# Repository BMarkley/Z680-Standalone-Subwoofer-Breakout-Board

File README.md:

# Z680-Standalone-Subwoofer-Breakout-Board

This is a pcb and circuit for repurposing the subwoofer in the Z680 Logitech speakers system with an aftermarket receiver. Good for keeping these speakers in service after the control pod fails.

The PCB has been tested and works great, but the design is provided with no garauntees or warranty. You are liable for your own actions.

Notes on the LED and enclosure: 

1: The enclosure took a little trial and error so use your best judgement. The original plan for the LED was to lave it illuminate the phono jack but the LED I selected was not bright enough to work like that. I had to bring it to the exterior of the case. Inconsistencies in the photos are just the trial and error process. 

2: I needed to use 2 washers on the potentiometer to get the Dsub connector to be at the correct depth.

3: You may want to use double sided tape to secure the final product to the back of the subwoofer. 

Licensing: Open Hardware licensed under the Creative Commons BY-SA 4.0 License

You are free to:
Share — copy and redistribute the material in any medium or format
Adapt — remix, transform, and build upon the material
The licensor cannot revoke these freedoms as long as you follow the license terms.
Under the following terms:
Attribution — You must give appropriate credit, provide a link to the license, and indicate if changes were made. You may do so in any reasonable manner, but not in any way that suggests the licensor endorses you or your use.

NonCommercial — You may not use the material for commercial purposes.

ShareAlike — If you remix, transform, or build upon the material, you must distribute your contributions under the same license as the original.

No additional restrictions — You may not apply legal terms or technological measures that legally restrict others from doing anything the license permits.

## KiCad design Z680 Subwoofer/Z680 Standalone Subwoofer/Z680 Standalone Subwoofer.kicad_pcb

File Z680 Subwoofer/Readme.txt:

This is a pcb and circuit for repurposing the subwoofer in the Z680 Logitech speakers system with an aftermarket receiver. Good for keeping these speakers in service after the control pod fails.

The PCB has been tested and works great, but the design is provided with no garauntees or warranty. You are liable for your own actions.

Notes on the LED and enclosure: 
1: The enclosure took a little trial and error so use your best judgement. The original plan for the LED was to lave it illuminate the phono jack but the LED I selected was not bright enough to work like that. I had to bring it to the exterior of the case. Inconsistencies in the photos are just the trial and error process. 
2: I needed to use 2 washers on the potentiometer to get the Dsub connector to be at the correct depth.
3: You may want to use double sided tape to secure the final product to the back of the subwoofer. 

Licensing: Open Hardware licensed under the Creative Commons BY-SA 4.0 License

You are free to:
Share — copy and redistribute the material in any medium or format
Adapt — remix, transform, and build upon the material
The licensor cannot revoke these freedoms as long as you follow the license terms.
Under the following terms:
Attribution — You must give appropriate credit, provide a link to the license, and indicate if changes were made. You may do so in any reasonable manner, but not in any way that suggests the licensor endorses you or your use.

NonCommercial — You may not use the material for commercial purposes.

ShareAlike — If you remix, transform, or build upon the material, you must distribute your contributions under the same license as the original.

No additional restrictions — You may not apply legal terms or technological measures that legally restrict others from doing anything the license permits.

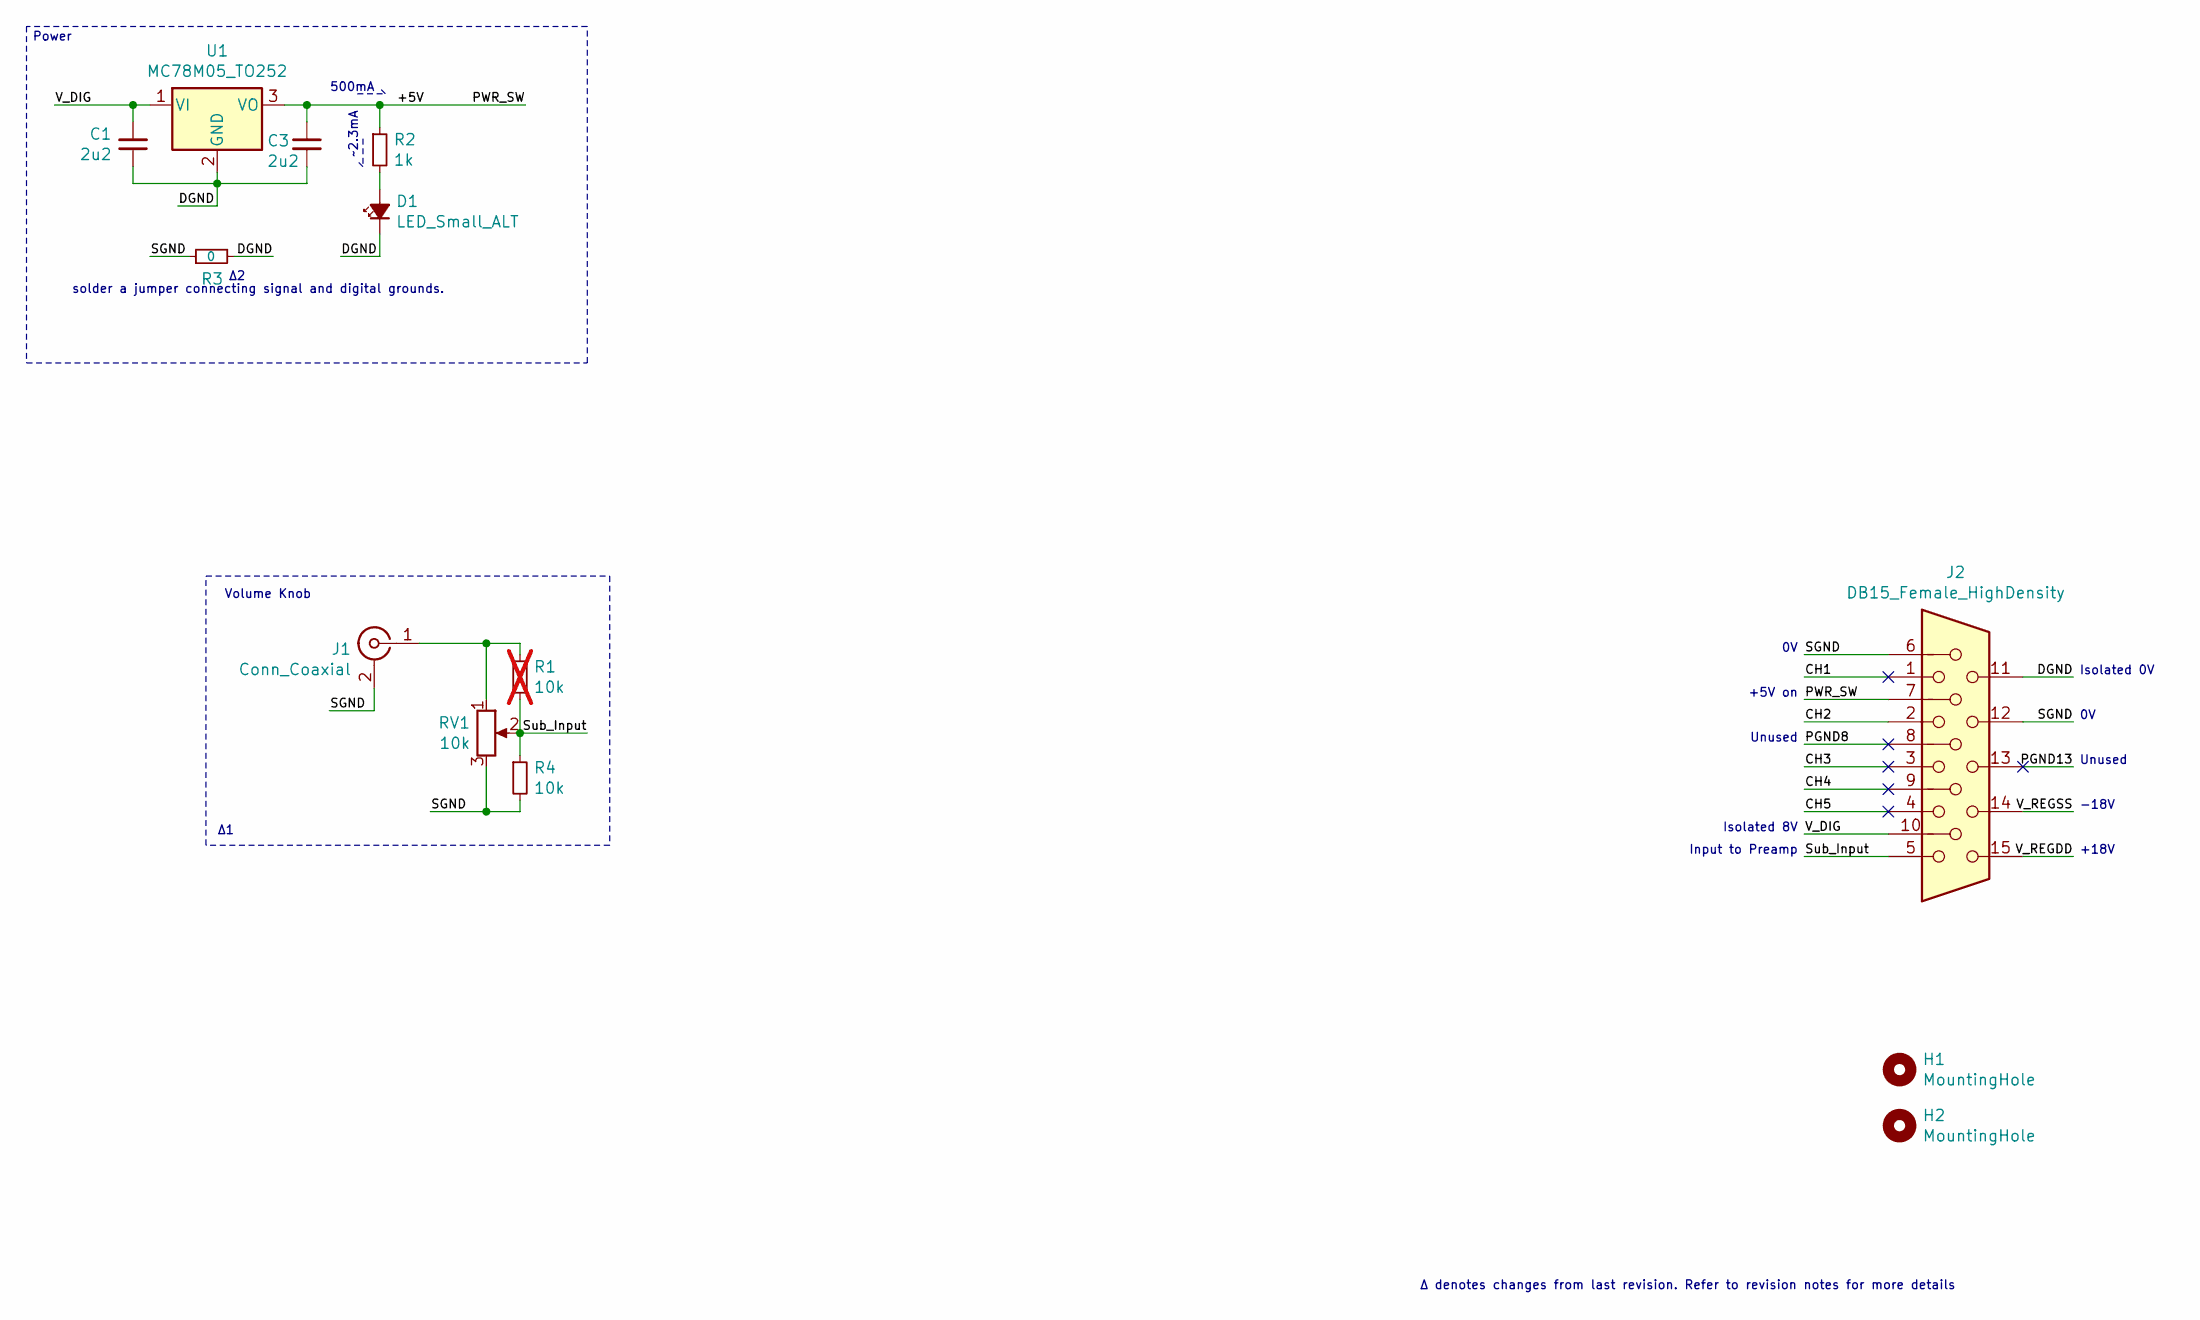
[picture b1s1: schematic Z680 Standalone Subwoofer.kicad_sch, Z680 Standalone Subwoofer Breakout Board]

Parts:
C1, C3: 2u2; C_0805_2012Metric
D1: LED_Small_ALT; LED_D3.0mm_Clear
H1, H2: MountingHole; MountingHole_2.2mm_M2
J1: Conn_Coaxial; RCJ-02
J2: DB15_Female_HighDensity; DSUB-15-HD_Female_Vertical_P2.29x1.98mm_MountingHoles
R1: 10k; R_0603_1608Metric; not fitted
R2: 1k; R_0603_1608Metric
R3: 0; R_0805_2012Metric
R4: 10k; R_0603_1608Metric
RV1: 10k; PotentiometerRecessed
U1: MC78M05_TO252; TO-252-2

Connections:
/+5V: C3.1, J2.7, R2.1, U1.3 (VO)
/CH1: J2.1
/CH2: J2.2
/CH3: J2.3
/CH4: J2.9
/CH5: J2.4
/DGND: C1.1, C3.2, D1.1 (K), J2.11, R3.2, U1.2 (GND)
/PGND8: J2.8
/PGND13: J2.13
/SGND: J1.2 (Ext), J2.6, J2.12, R3.1, R4.2, RV1.3
/Sub_Input: J2.5, R1.2, R4.1, RV1.2
/V_DIG: C1.2, J2.10, U1.1 (VI)
/V_REGDD: J2.15
/V_REGSS: J2.14
unnamed: D1.2 (A), R2.2
unnamed: J1.1 (In), R1.1, RV1.1

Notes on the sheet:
Input to Preamp
solder a jumper connecting signal and digital grounds.
~2.3mA
Volume Knob
-18V
Unused
500mA
Power
+18V
Δ denotes changes from last revision. Refer to revision notes for more details
Isolated 8V
+5V on
Isolated 0V

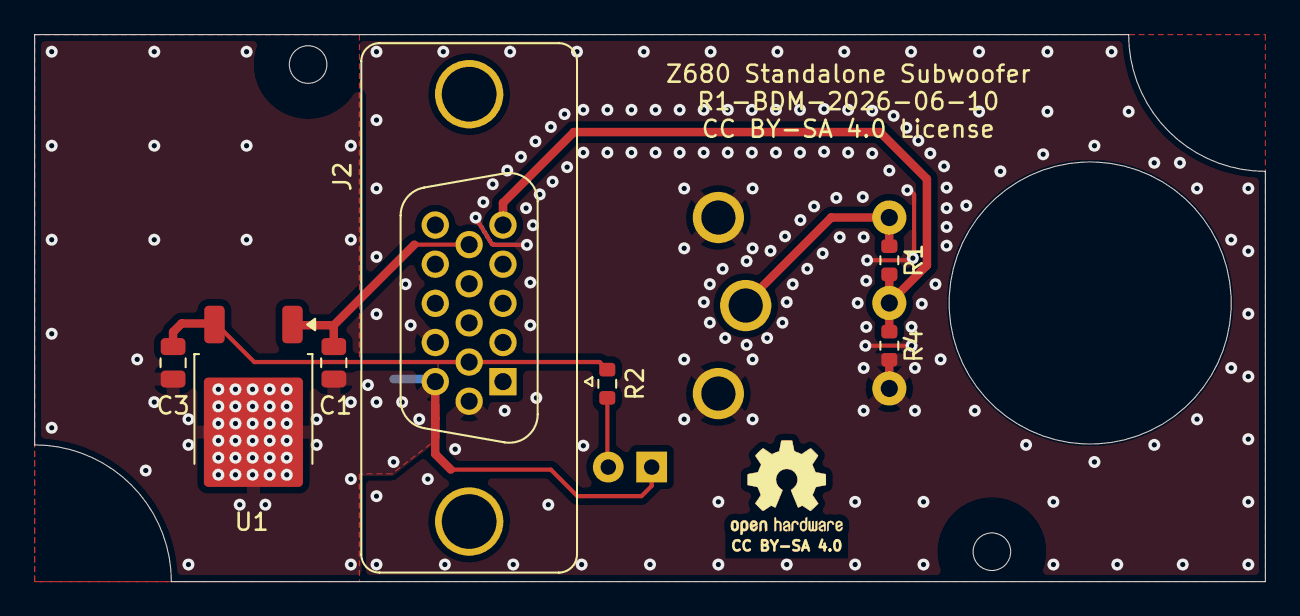
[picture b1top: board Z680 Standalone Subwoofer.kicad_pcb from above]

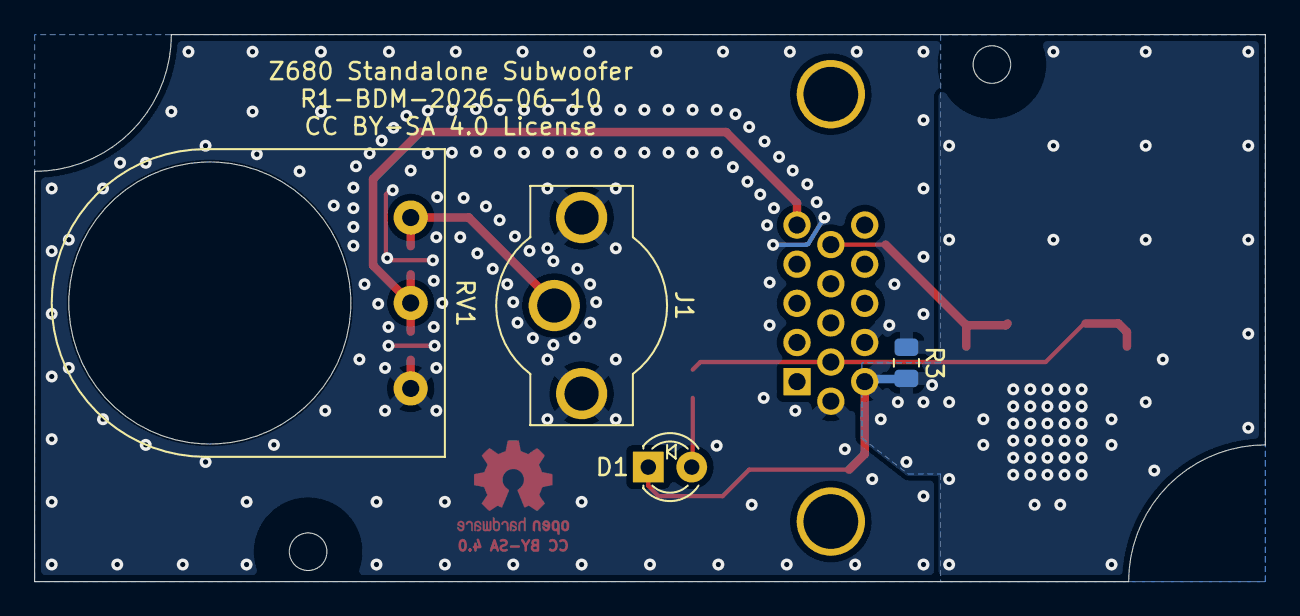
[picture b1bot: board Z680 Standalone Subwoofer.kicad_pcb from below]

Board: 2 copper layers, 72.0 x 32.0 mm, 13 parts (4 on the bottom side), 7 nets.

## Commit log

2026-06-10 Reuploaded Kicad files
    Reuploaded Kicad files in response to issue #1
2026-06-10 Reupload Kicad Files
    Reupload kicad files in response to issue #1
2026-06-11 Kicad 10 upload
    Saved the files in Kicad 10.
2026-06-11 Updated Gerbers
    R2 was mislabelled C2 on the Gerbers for some reason.
2026-06-12 Gain calculations for R1 of the PCB
2026-06-12 Revision 1
    Fix low end gain on volume

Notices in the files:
Z680 Subwoofer/Z680 Standalone Subwoofer/Z680 Standalone Subwoofer.kicad_pcb:
CC BY-SA 4.0 License
CC BY-SA 4.0
